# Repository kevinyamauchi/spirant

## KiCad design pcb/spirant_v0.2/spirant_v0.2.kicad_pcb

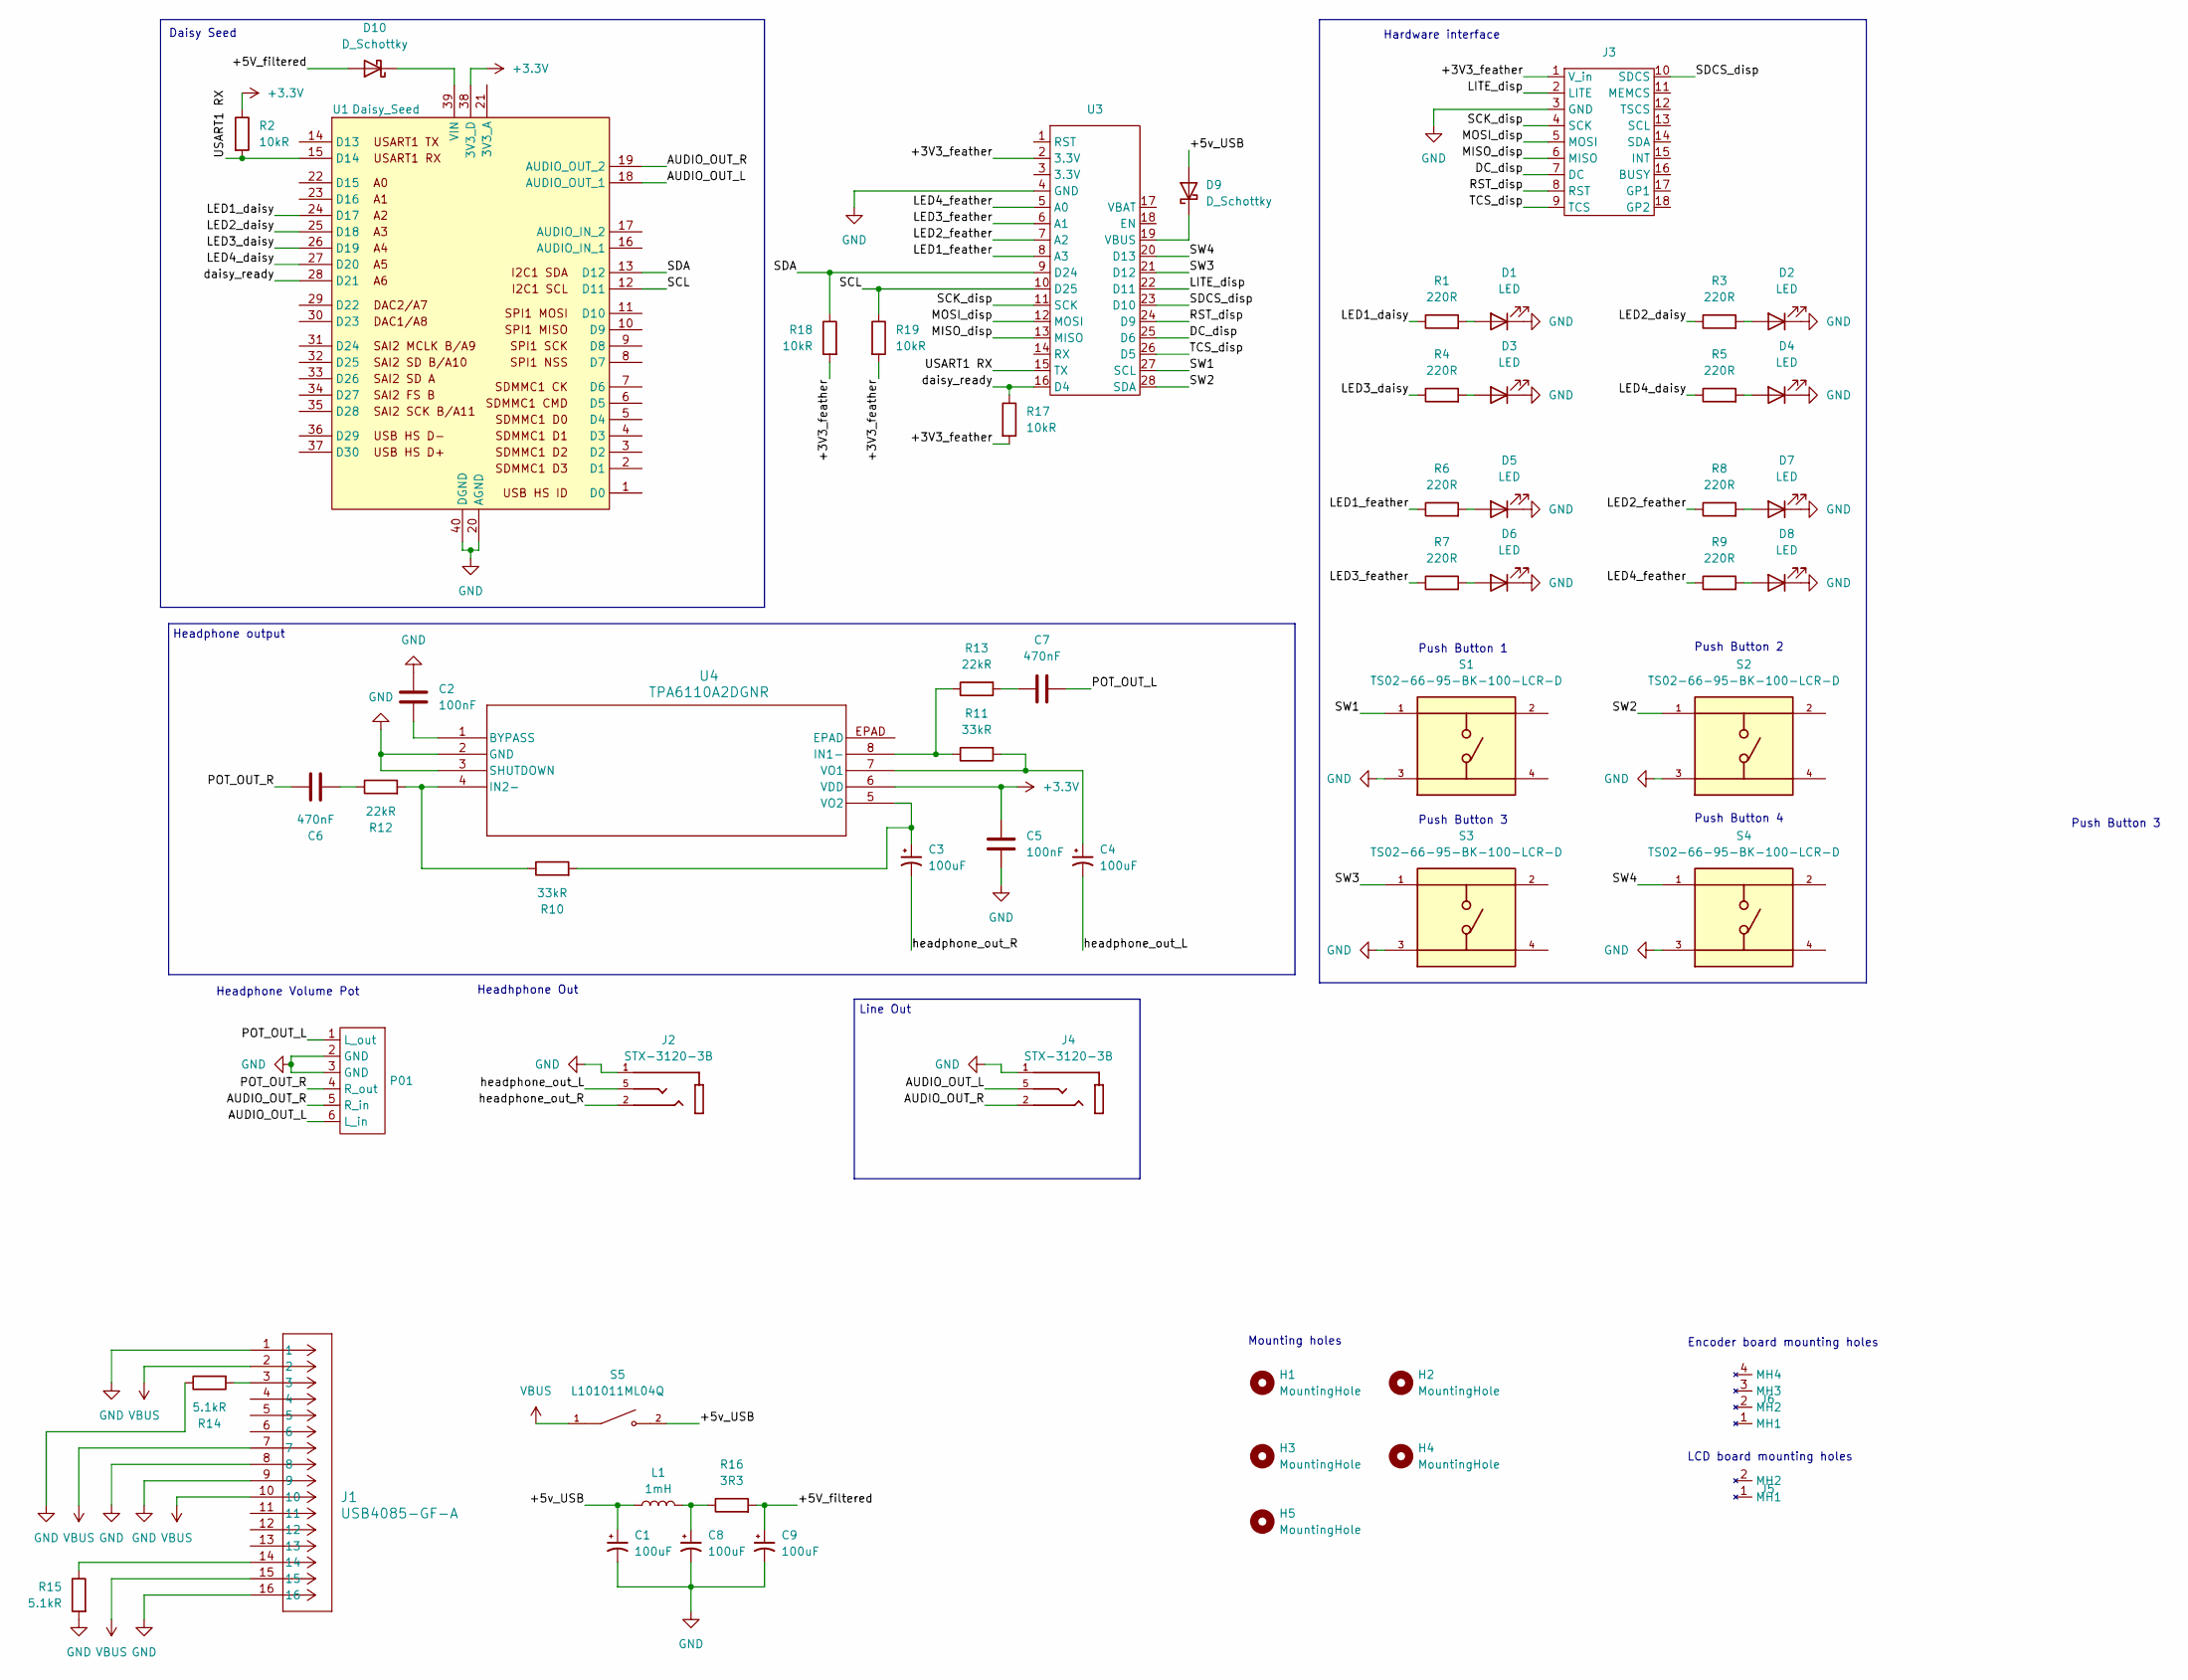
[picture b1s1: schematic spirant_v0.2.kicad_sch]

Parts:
C1, C3, C4, C8, C9: 100uF; CP_Radial_D10.0mm_P5.00mm
C2, C5: 100nF; C_Disc_D5.0mm_W2.5mm_P5.00mm
C6, C7: 470nF; C_Disc_D5.0mm_W2.5mm_P2.50mm
D1, D2, D3, D4, D5, D6, D7, D8: LED; LED_D3.0mm
D9, D10: D_Schottky; D_A-405_P7.62mm_Horizontal
H1, H2, H3, H4, H5: MountingHole; MountingHole_3.2mm_M3_Pad
J1: USB4085-GF-A; CONN16_USB4085-GF-A_GCT
J2, J4: STX-3120-3B; KYCON_STX-3120-3B; PARTREV B3
J3: eyespi_breakout
J5: adafruit_ips_tf2_board
J6: adafruit_quad_encoder_board
L1: 1mH; L_Axial_L16.0mm_D7.5mm_P25.40mm_Horizontal_Fastron_XHBCC
P01: RK12L12C0A0E
R1, R3, R4, R5, R6, R7, R8, R9: 220R; R_Axial_DIN0207_L6.3mm_D2.5mm_P7.62mm_Horizontal
R2, R17, R18, R19: 10kR; R_Axial_DIN0207_L6.3mm_D2.5mm_P7.62mm_Horizontal
R10, R11: 33kR; R_Axial_DIN0207_L6.3mm_D2.5mm_P7.62mm_Horizontal
R12, R13: 22kR; R_Axial_DIN0207_L6.3mm_D2.5mm_P7.62mm_Horizontal
R14, R15: 5.1kR; R_Axial_DIN0207_L6.3mm_D2.5mm_P7.62mm_Horizontal
R16: 3R3; R_Axial_DIN0207_L6.3mm_D2.5mm_P7.62mm_Horizontal
S1, S2, S3, S4: TS02-66-95-BK-100-LCR-D; SW_TS02-66-95-BK-100-LCR-D; PARTREV 1.0
S5: L101011ML04Q; SW_L101011ML04Q; PARTREV 19 Mar 2019
U1: Daisy_Seed; DAISY_SEED
U3: adafruit_feather_rp2040
U4: TPA6110A2DGNR; DGN8_1P89X1P57

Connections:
+3.3V: C5.1, R2.1, U1.38 (3V3_D), U4.6 (VDD)
/+3V3_feather: J3.1 (V_in), R17.2, R18.2, R19.2, U3.2 (3.3V)
/+5V_filtered: C9.1, D10.2 (A), R16.2
/+5v_USB: C1.1, D9.2 (A), L1.1, S5.2
/AUDIO_OUT_L: J4.5, P01.6 (L_in), U1.18 (AUDIO_OUT_1)
/AUDIO_OUT_R: J4.2, P01.5 (R_in), U1.19 (AUDIO_OUT_2)
/DC_disp: J3.7 (DC), U3.25 (D6)
/LED1_daisy: R1.1, U1.24 (D17)
/LED1_feather: R6.1, U3.8 (A3)
/LED2_daisy: R3.1, U1.25 (D18)
/LED2_feather: R8.1, U3.7 (A2)
/LED3_daisy: R4.1, U1.26 (D19)
/LED3_feather: R7.1, U3.6 (A1)
/LED4_daisy: R5.1, U1.27 (D20)
/LED4_feather: R9.1, U3.5 (A0)
/LITE_disp: J3.2 (LITE), U3.22 (D11)
/MISO_disp: J3.6 (MISO), U3.13 (MISO)
/MOSI_disp: J3.5 (MOSI), U3.12 (MOSI)
/POT_OUT_L: C7.2, P01.1 (L_out)
/POT_OUT_R: C6.2, P01.4 (R_out)
/RST_disp: J3.8 (RST), U3.24 (D9)
/SCK_disp: J3.4 (SCK), U3.11 (SCK)
/SCL: R19.1, U1.12 (D11), U3.10 (D25)
/SDA: R18.1, U1.13 (D12), U3.9 (D24)
/SDCS_disp: J3.10 (SDCS), U3.23 (D10)
/SW1: S1.1, U3.27 (SCL)
/SW2: S2.1, U3.28 (SDA)
/SW3: S3.1, U3.21 (D12)
/SW4: S4.1, U3.20 (D13)
/TCS_disp: J3.9 (TCS), U3.26 (D5)
/USART1 RX: R2.2, U1.15 (D14), U3.15 (TX)
/daisy_ready: R17.1, U1.28 (D21), U3.16 (D4)
/headphone_out_L: C4.2, J2.5
/headphone_out_R: C3.2, J2.2
<NO NET>: C1.2, C2.1, C5.2, C8.2, C9.2, D1.1 (K), D2.1 (K), D3.1 (K), D4.1 (K), D5.1 (K), D6.1 (K), D7.1 (K), D8.1 (K), J1.1, J1.8, J1.9, J1.16, J2.1, J3.3 (GND), J4.1, P01.2 (GND), P01.3 (GND), R14.1, R15.2, S1.3, S2.3, S3.3, S4.3, U1.20 (AGND), U1.40 (DGND), U3.4 (GND), U4.2 (GND), U4.3 (SHUTDOWN)
unnamed: C6.1, R12.1
unnamed: C7.1, R13.2
unnamed: C8.1, L1.2, R16.1
unnamed: D1.2 (A), R1.2
unnamed: D2.2 (A), R3.2
unnamed: D3.2 (A), R4.2
unnamed: D4.2 (A), R5.2
unnamed: D5.2 (A), R6.2
unnamed: D6.2 (A), R7.2
unnamed: D7.2 (A), R8.2
unnamed: D8.2 (A), R9.2
unnamed: D9.1 (K), U3.19 (VBUS)
unnamed: D10.1 (K), U1.39 (VIN)
unnamed: J1.3, R14.2
unnamed: J1.14, R15.1
unnamed: C2.2, U4.1 (BYPASS)
unnamed: R11.1, R13.1, U4.8 (IN1-)
unnamed: R10.1, R12.2, U4.4 (IN2-)
unnamed: C4.1, R11.2, U4.7 (VO1)
unnamed: C3.1, R10.2, U4.5 (VO2)
VBUS: J1.2, J1.7, J1.10, J1.15, S5.1

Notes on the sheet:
Mounting holes
Hardware interface
Daisy Seed
LCD board mounting holes
Push Button 1
Push Button 2
Line Out
Push Button 4
Encoder board mounting holes
Push Button 3
Headphone Volume Pot
Headphone output
Headhphone Out

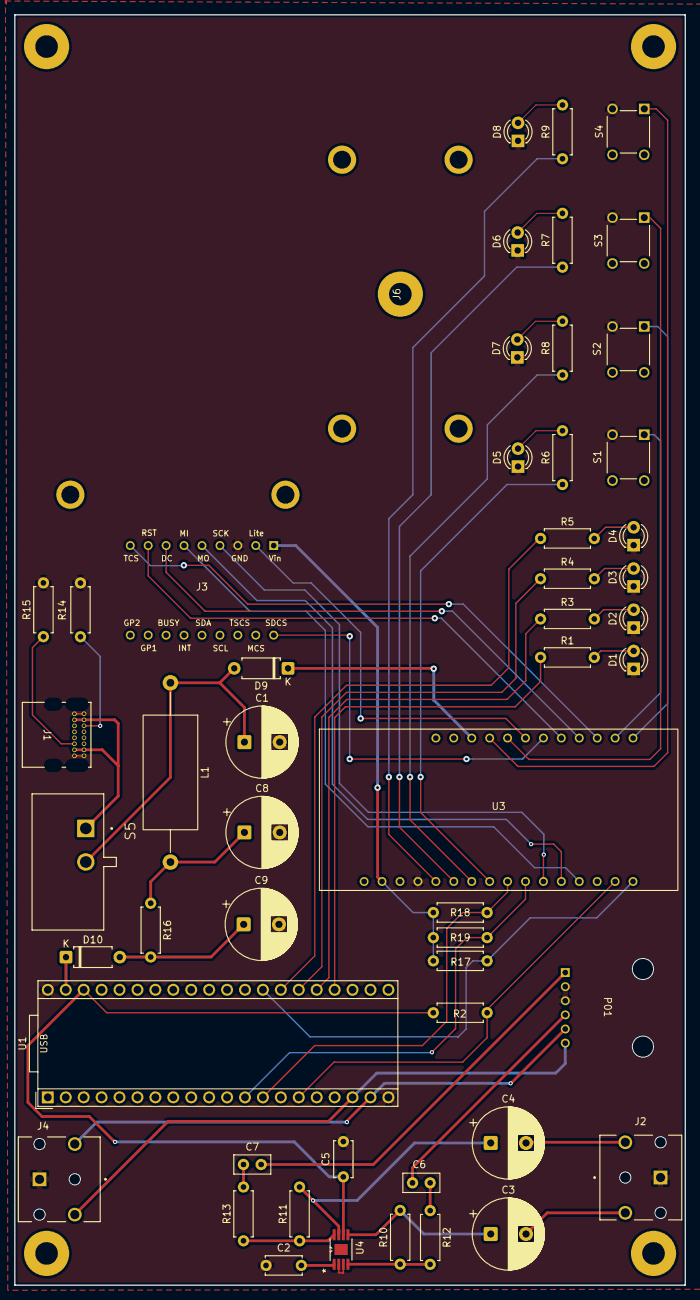
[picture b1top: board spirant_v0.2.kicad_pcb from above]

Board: 4 copper layers, 95.0 x 180.0 mm, 59 parts (0 on the bottom side), 56 nets.

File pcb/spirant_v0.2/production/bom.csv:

Designator,Footprint,Quantity,Value,LCSC Part #
"C1, C3, C4, C8, C9",CP_Radial_D10.0mm_P5.00mm,5,100uF,
"C2, C5",C_Disc_D5.0mm_W2.5mm_P5.00mm,2,100nF,
"C6, C7",C_Disc_D5.0mm_W2.5mm_P2.50mm,2,470nF,
"D1, D2, D3, D4, D5, D6, D7, D8",LED_D3.0mm,8,LED,
"D10, D9",D_A-405_P7.62mm_Horizontal,2,D_Schottky,
J1,CONN16_USB4085-GF-A_GCT,1,USB4085-GF-A,
"J2, J4",KYCON_STX-3120-3B,2,STX-3120-3B,
J5,adafruit_ips_tf2_board,1,~,
J6,adafruit_quad_encoder_board,1,~,
L1,L_Axial_L16.0mm_D7.5mm_P25.40mm_Horizontal_Fastron_XHBCC,1,1mH,
"R1, R3, R4, R5, R6, R7, R8, R9",R_Axial_DIN0207_L6.3mm_D2.5mm_P7.62mm_Horizontal,8,220R,
"R10, R11",R_Axial_DIN0207_L6.3mm_D2.5mm_P7.62mm_Horizontal,2,33kR,
"R12, R13",R_Axial_DIN0207_L6.3mm_D2.5mm_P7.62mm_Horizontal,2,22kR,
"R14, R15",R_Axial_DIN0207_L6.3mm_D2.5mm_P7.62mm_Horizontal,2,5.1kR,
R16,R_Axial_DIN0207_L6.3mm_D2.5mm_P7.62mm_Horizontal,1,3R3,
"R17, R18, R19, R2",R_Axial_DIN0207_L6.3mm_D2.5mm_P7.62mm_Horizontal,4,10kR,
"S1, S2, S3, S4",SW_TS02-66-95-BK-100-LCR-D,4,TS02-66-95-BK-100-LCR-D,
S5,SW_L101011ML04Q,1,L101011ML04Q,
U1,DAISY_SEED,1,Daisy_Seed,
U3,adafruit_feather_rp2040,1,~,
U4,DGN8_1P89X1P57,1,TPA6110A2DGNR,

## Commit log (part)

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2026-02-14 add initial synth software
2026-02-14 add initial synth software (#1)
2026-02-14 remove build files
2026-02-15 add encoder firmware
2026-02-15 Add encoder driver (#2)
    * remove build files
    * add encoder firmware
2026-02-16 add target folder to gitignore
2026-02-16 add oled driver
2026-02-16 Add oled driver (#3)
    * add target folder to gitignore
    * add target folder to gitignore
    * add oled driver
2026-02-16 add integration example
2026-02-16 integrate encoder and LED (#4)
    * add target folder to gitignore
    * add target folder to gitignore
    * add oled driver
    * add integration example
2026-03-26 update ui
